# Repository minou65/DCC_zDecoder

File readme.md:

# DCC zDecoder

- [DCC zDecoder](#dcc-zdecoder)
	- [Beschreibung](#beschreibung)
	- [Platinen](#platinen)
	- [Librarys](#librarys)
	- [Pin mapping](#pin-mapping)
	- [Betriebsarten](#betriebsarten)
		- [in Vorbereitung](#in-vorbereitung)
	- [Schema](#schema)
	- [Materialliste](#materialliste)
	- [Anschlüsse](#anschlüsse)
	- [Inbetriebnahme](#inbetriebnahme)
	- [Web UI](#web-ui)
		- [Overview](#overview)
		- [Groups](#groups)
		- [Config](#config)
	- [WiFi](#wifi)
		- [Default Password](#default-password)
		- [Default IP address](#default-ip-address)
		- [OTA](#ota)
		- [Configuration options](#configuration-options)
		- [Blinking codes](#blinking-codes)
	- [Firmware](#firmware)
	- [Reset](#reset)

## Beschreibung
Das ist ein NRMA DCC dekoder basirend auf einem ESP32 NodeMCU. 
- Er kann bis zu 16 Ausgänge ansteuern. 
- Stellt eine Wifi AP zur verfügung oder kann in Wifi Netz integriert werden
- Wird via Web UI konfiguriert
- Kann via DCC oder Web UI gesteuert werden

Der Decoder kann an einer Spannung von 8 - 28V DC oder 18 - 36V AC betrieben werden. Pro Ausgang 
kann eine Last von 500mA geschaltet werden. Ist J1 auf der Stellung 5V, darf der gesamt Strom 1A
nicht übersteigen.

[Top of document](#dcc-zdecoder)

## Platinen
Unbestückte Platinen sind bei mir erhältlich für CHF 5.00 / Stück plus Porto. Bestückte Platinen CHF 30.00 plus Porto
[Top of document](#dcc-zdecoder)

## Librarys
Die folgenden Bibliotheken werden verwendet und müssen installiert werden
- [NMRA DCC](https://github.com/mrrwa/NmraDcc)
- [IotWebConf (3.2.3)](https://github.com/minou65/IotWebConf)
- [IotWebRoot](https://github.com/minou65/IotWebRoot)

[Top of document](#dcc-zdecoder)

## Pin mapping
In der Header datei [pinmapping.h](src/pinmapping.h) können die Pins für die 16 Ausgänge an die eigenen Bedürfnisse angepasst werden.

```cpp
static uint8_t ChannelToGPIOMapping[16] = {
	GPIO_NUM_23, // O11
	GPIO_NUM_22, // O12
	GPIO_NUM_21, // O13
	GPIO_NUM_19, // O14
	GPIO_NUM_18, // O15
	GPIO_NUM_17, // O16
	GPIO_NUM_16, // O17
	GPIO_NUM_4,  // O18

	GPIO_NUM_33, // O21
	GPIO_NUM_32, // O22
	GPIO_NUM_25, // O23
	GPIO_NUM_26, // O24
	GPIO_NUM_27, // O25
	GPIO_NUM_14, // O26
	GPIO_NUM_12, // O27
	GPIO_NUM_13  // O28

};
```
[Top of document](#dcc-zdecoder)

## Betriebsarten

Der zDecoder untersützt folgende Betriebsarten
- [Watchdog](doc/watchdog.md#watchdog-1)
- [einfacher Ausgang](doc/blinkers.md#einfacher-ausgang)
- [Blinker](doc/blinkers.md#blinker)
- [Wechselblinker](doc/blinkers.md#wechselblinker)
- [Fernseher](doc/blinkers.md#fernseher)
- [Schweisslicht](doc/blinkers.md#schweissen)
- [Feuer](doc/blinkers.md#feuer)
- [Blitzlicht](doc/blinkers.md#blitzlicht)
- [Lauflicht 1](doc/blinkers.md#lauflicht-1)
- [Lauflicht 2](doc/blinkers.md#lauflicht-2)
- [Lauflicht 3](doc/blinkers.md#lauflicht-3)
- [Lauflicht 4](doc/blinkers.md#lauflicht-4)
- [Hausbeleuchtung](doc/blinkers.md#hausbeleuchtung)
- [Neonlampen](doc/blinkers.md#neon-lampe)
- [Natriumlampen](doc/blinkers.md#natrium-lampe)
- [Entkuppler](doc/coils.md#entkuppler)
- [Weiche](doc/coils.md#weiche)
- [Servo](doc/servo.md#servo-1)

[Top of document](#dcc-zdecoder)

### in Vorbereitung
- SBB Hauptsignal 2 flammig
- SBB Hauptsignal 3 flammig
- SBB Hauptsignal 4 flammig
- SBB Hauptsignal 5 flammig
- SBB Zwergsignal
- Strassensignal

[Top of document](#dcc-zdecoder)

## Schema

## Materialliste

[Partliste](sch/partlist.txt)

[Top of document](#dcc-zdecoder)

## Anschlüsse

| Klemmenblock | Beschreibung |
| --- | --- |
| X1 - X2 | + Anschluss für Verbraucher 5/12-28VDc, je nach position von J1 |
| X3 - X4 | - Anschluss für Verbraucher |
| X5 | DCC signal |
| X6 | Anschluss versorgungspannung für Decoder und Verbraucher. 12 - 28VDC/AC |
| X7 - X12 | Anschluss für Servos |

[Top of document](#dcc-zdecoder)

## Inbetriebnahme

Nachdem alles zusammengebaut ist und alle Lötstellen sorgfältig überprüft wurden, kann das Program auf den ESP aufgespielt werden.
Lauflicht 2

[Top of document](#dcc-zdecoder)

## Web UI

Mittels des Web User interfaces kann der zDecoder einfach konfiguriert und bedient werden

### Overview

auf dieser Seite sind alle wichtigen Informationn zu zDecoder ersichtlich

[Top of document](#dcc-zdecoder)

### Groups

auf dieser Seite können die Gruppen ein und ausgescahltet werden. Wird über DCC geschaltet, ist auf dieser Seite auch der jeweilige Status ersichtlich. Rot ist ausgeschaltet, grün ist eingeschaltet

[Top of document](#dcc-zdecoder)

### Config

auf dieser Seite können die Gruppen erstellt und konfiguriert werden. Die Bedeutung und Verwendung der Parameter ist beim jeweiligen Objekt unter [Betriebsarten](#betriebsarten) beschrieben.

[Top of document](#dcc-zdecoder)

## WiFi

### Default Password

Wenn nicht mit einem AP verbunden, ist das Standardpasswort 123456789

[Top of document](#dcc-zdecoder)

### Default IP address

Wenn nicht mit einem AP verbunden, ist die IP Adresse 192.168.4.1

[Top of document](#dcc-zdecoder)

### OTA 
OTA ist aktiviert und kann verwenbdet werden. Damit ist es möglich, die Software des zDecoders zu updaten ohne unter die Anlage krichen zu müssen. Die IP Adresse ist entweder die Default IP address oder die vom AP zugewissene. Port ist Standart

[Top of document](#dcc-zdecoder)

### Configuration options
Nach dem ersten Start müssen einige Werte eingerichtet werden.

| Parameter | Beschreibung |
|---|---|
| Thing name | Name des Decoders. Es sollten keine Sonderzeichen und <br> Umlaute verwendet werden. Punkte und Leerzeichen sollten <br> ebenfalls nicht verwendet werden.
| AP password | Dieses Passwort wird verwendet, wenn Sie später auf <br> das Gerät zugreifen möchten. Sie müssen ein Passwort <br> mit mindestens 8, höchstens 32 Zeichen verwenden. <br> Es steht Ihnen frei, beliebige Zeichen zu verwenden, <br> Es sollte ein Passwort mit mindestens 12 Zeichen Länge gewählt werden. |
| WiFi SSID | Name des WLan mit welchem das thing verwendet werden soll. |
| WiFi password | Das Passwort zum Netzwerk, mit welchem das Thing verbunden werden soll. |

[Top of document](#dcc-zdecoder)

### Blinking codes

In der nachfolgenden Tabelle fasst die verschiedenen Blinkcodes zusammen

| Code | Bedeutung |
|---|---|
| rasches blinken | meisten ein, unterbrochen durch kurze aus perioden. <br> Eigener AP ist aktiviert und sie können mit <br> dem Smartphone oder einem Computer eine<br> Verbindung zum Thing herstellen. |
| wechsel blinken | Das Thing versucht mit einem AP zu verbinden |
| langsames blinken | meistens aus mit kurzem blinken <br> Das Thing ist online und mit dem WLan verbunden |

[Top of document](#dcc-zdecoder)

## Firmware
Hier kann, eine entsprechende Datei vorausgesetzt, die Firmware des decoders aktualisiert werden

## Reset
Wurde das Passwort vergessen oder funktioniert der Decoder nicht mehr kann durch schliessen des Jumpers Reset während dem booten, der Decoder auf die Werkseinstellungen zurückgesetzt werden.

[Top of document](#dcc-zdecoder)

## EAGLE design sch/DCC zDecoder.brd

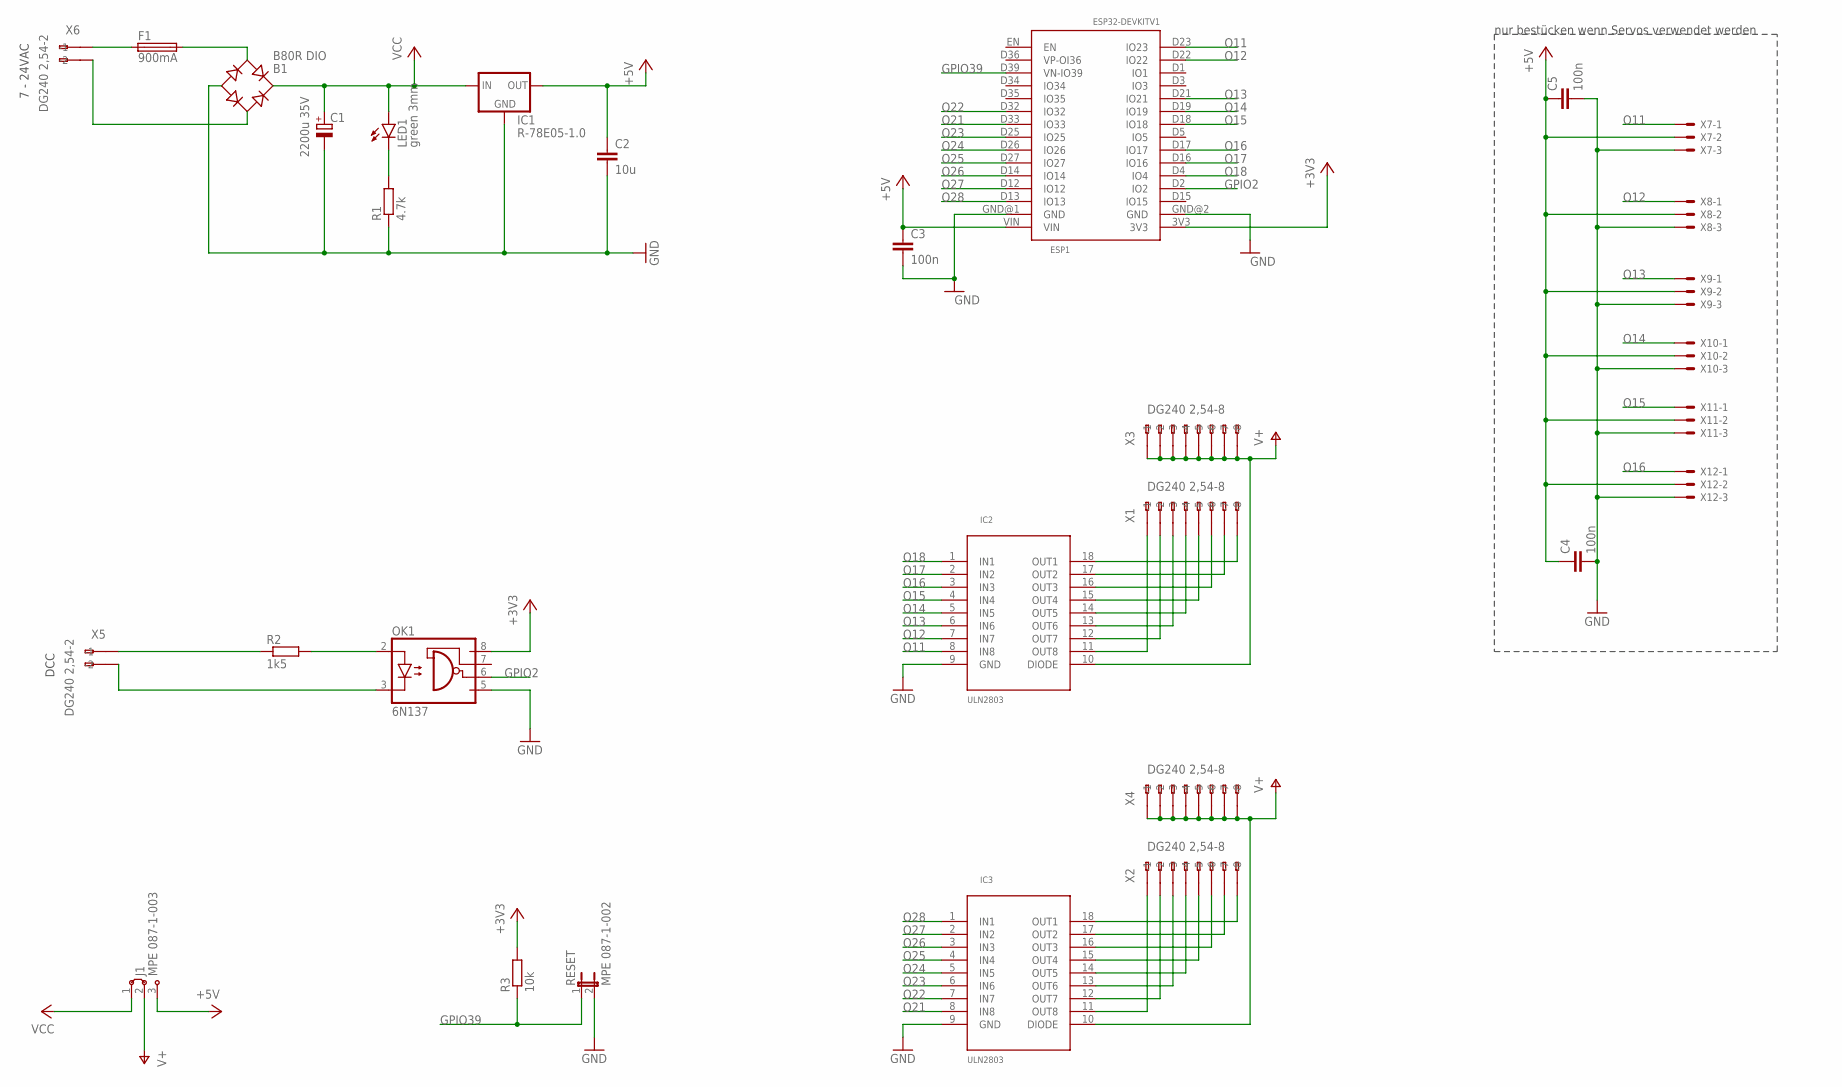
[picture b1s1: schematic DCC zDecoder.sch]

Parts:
B1: B80R DIO; RB1A
C1: 2200u 35V; E5-8,5
C2: 10u; C050-024X044
C3, C4, C5: 100n; C050-024X044
ESP1: ESP32DEVKITV1; ESP32-DEVKITV1
F1: 900mA; TE5
IC1: R-78E05-1.0; R-78E-XX1.0
IC2, IC3: ULN2803; DIL18
J1: MPE 087-1-003; 04C
LED1: green 3mm; LED3MM
OK1: 6N137; DIL08
R1: 4.7k; 0207/10
R2: 1k5; 0207/10
R3: 10k; 0207/10
RESET: MPE 087-1-002; JP1
X1, X2, X3, X4: DG240 2,54-8; 233-508
X5, X6: DG240 2,54-2; 233-202
X7, X8, X9, X10, X11, X12: PSS 254/3G; 22-23-2031

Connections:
+3V3: ESP1.3V3, OK1.8 (VCC), R3.2
+5V: C2.1, C3.1, C4.1, C5.1, ESP1.VIN, IC1.OUT, J1.3, X7.2, X8.2, X9.2, X10.2, X11.2, X12.2
GND: B1.-, C1.-, C2.2, C3.2, C4.2, C5.2, ESP1.GND@1 (GND), ESP1.GND@2 (GND), IC1.GND, IC2.9 (GND), IC3.9 (GND), OK1.5 (GND), R1.1, RESET.2, X7.3, X8.3, X9.3, X10.3, X11.3, X12.3
GPIO2: ESP1.D2 (IO2), OK1.6 (VO)
GPIO39: ESP1.D39 (VN-IO39), R3.1, RESET.1
unnamed: IC2.11 (OUT8), X1.A1 (-1)
unnamed: IC2.12 (OUT7), X1.A2 (-2)
unnamed: LED1.K (C), R1.2
unnamed: IC2.13 (OUT6), X1.A3 (-3)
unnamed: B1.AC1, F1.2
unnamed: B1.AC2, X6.A2 (-2)
unnamed: IC2.14 (OUT5), X1.A4 (-4)
unnamed: IC2.15 (OUT4), X1.A5 (-5)
unnamed: R2.1, X5.A1 (-1)
unnamed: OK1.2 (A), R2.2
unnamed: OK1.3 (C), X5.A2 (-2)
unnamed: IC2.16 (OUT3), X1.A6 (-6)
unnamed: IC2.17 (OUT2), X1.A7 (-7)
unnamed: IC2.18 (OUT1), X1.A8 (-8)
unnamed: F1.1, X6.A1 (-1)
unnamed: IC3.18 (OUT1), X2.A8 (-8)
unnamed: IC3.17 (OUT2), X2.A7 (-7)
unnamed: IC3.16 (OUT3), X2.A6 (-6)
unnamed: IC3.15 (OUT4), X2.A5 (-5)
unnamed: IC3.14 (OUT5), X2.A4 (-4)
unnamed: IC3.13 (OUT6), X2.A3 (-3)
unnamed: IC3.12 (OUT7), X2.A2 (-2)
unnamed: IC3.11 (OUT8), X2.A1 (-1)
O11: ESP1.D23 (IO23), IC2.8 (IN8), X7.1
O12: ESP1.D22 (IO22), IC2.7 (IN7), X8.1
O13: ESP1.D21 (IO21), IC2.6 (IN6), X9.1
O14: ESP1.D19 (IO19), IC2.5 (IN5), X10.1
O15: ESP1.D18 (IO18), IC2.4 (IN4), X11.1
O16: ESP1.D17 (IO17), IC2.3 (IN3), X12.1
O17: ESP1.D16 (IO16), IC2.2 (IN2)
O18: ESP1.D4 (IO4), IC2.1 (IN1)
O21: ESP1.D33 (IO33), IC3.8 (IN8)
O22: ESP1.D32 (IO32), IC3.7 (IN7)
O23: ESP1.D25 (IO25), IC3.6 (IN6)
O24: ESP1.D26 (IO26), IC3.5 (IN5)
O25: ESP1.D27 (IO27), IC3.4 (IN4)
O26: ESP1.D14 (IO14), IC3.3 (IN3)
O27: ESP1.D12 (IO12), IC3.2 (IN2)
O28: ESP1.D13 (IO13), IC3.1 (IN1)
V+: IC2.10 (DIODE), IC3.10 (DIODE), J1.2, X3.A1 (-1), X3.A2 (-2), X3.A3 (-3), X3.A4 (-4), X3.A5 (-5), X3.A6 (-6), X3.A7 (-7), X3.A8 (-8), X4.A1 (-1), X4.A2 (-2), X4.A3 (-3), X4.A4 (-4), X4.A5 (-5), X4.A6 (-6), X4.A7 (-7), X4.A8 (-8)
VCC: B1.+, C1.+, IC1.IN, J1.1, LED1.A

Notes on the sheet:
7 - 24VAC
DCC
nur bestücken wenn Servos verwendet werden

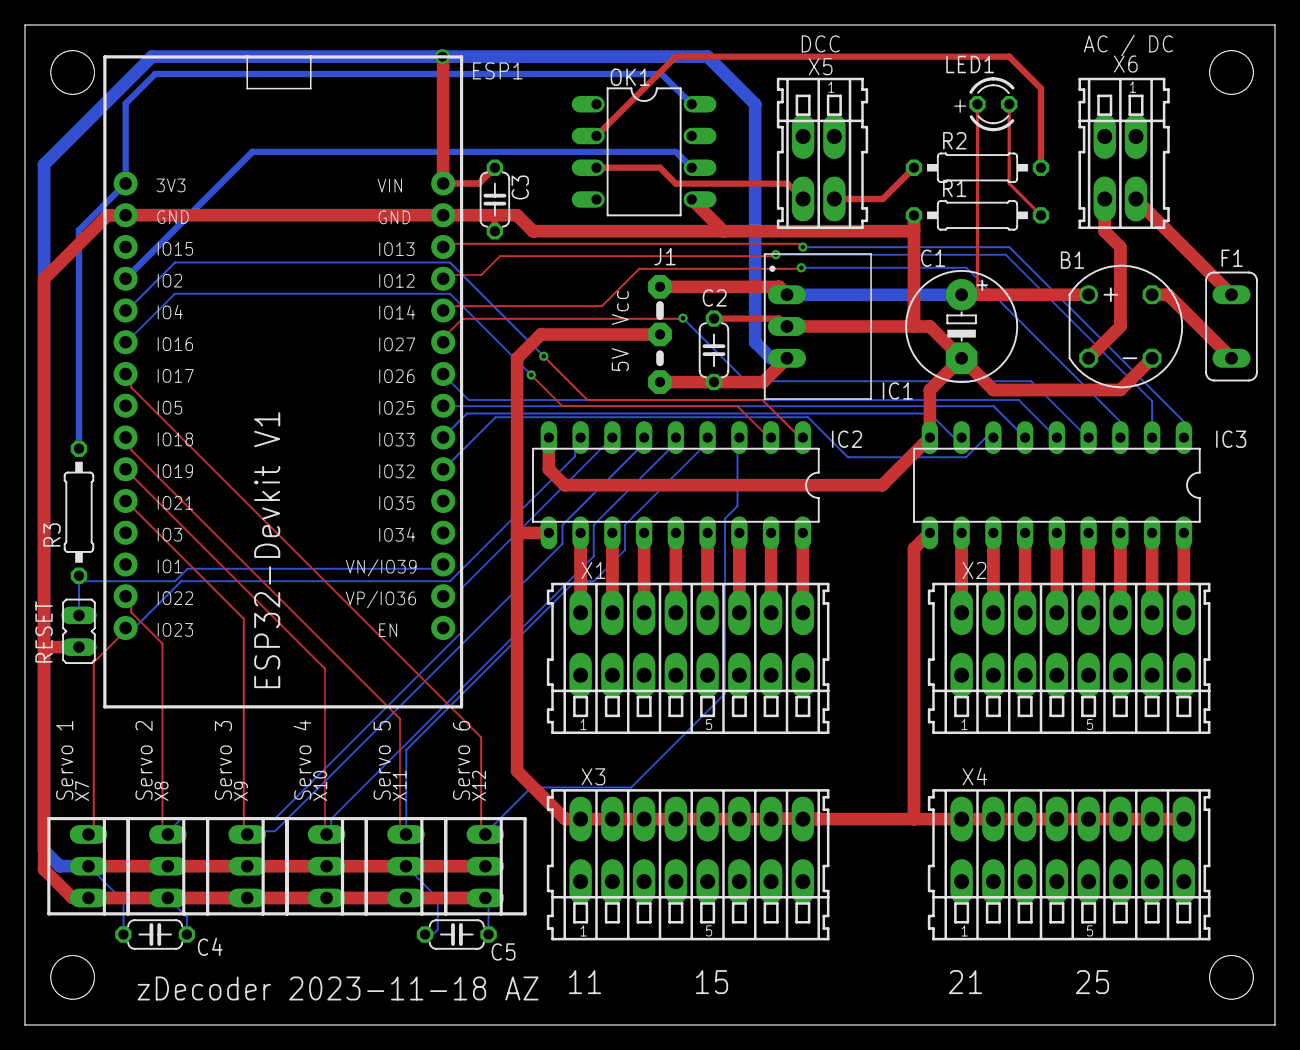
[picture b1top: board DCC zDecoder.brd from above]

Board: 2 copper layers, 100.0 x 80.0 mm, 30 parts (0 on the bottom side), 46 nets.

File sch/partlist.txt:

Partlist

Exported from DCC zDecoder.sch at 18.11.2023 09:42

EAGLE Version 9.6.2 Copyright (c) 1988-2020 Autodesk, Inc.

Assembly variant: 

Part     Value          Device        Package        Library     Sheet

B1       B80R DIO       RB1A          RB1A           rectifier   1
C1       2200u 35V      CPOL-EUE5-8.5 E5-8,5         rcl         1
F1       900mA          TE5           TE5            fuse        1
IC1      TSR 1-2450     78XXS         78XXS          v-reg       1
IC2      ULN2803        ULN2803DIL18  DIL18          _eigene     1
IC3      ULN2803        ULN2803DIL18  DIL18          _eigene     1
J1       MPE 087-1-003  J2X2MM        04C            jumper      1
LED1     green 3mm      TLLG4400      LED3MM         led         1
OK1      6N137          6N137         DIL08          optocoupler 1
R1       4.7k           R-EU_0207/10  0207/10        rcl         1
R2       1k5            R-EU_0207/10  0207/10        rcl         1
R3       10k            R-EU_0207/10  0207/10        rcl         1
RESET    MPE 087-1-002  JP1E          JP1            jumper      1
U$1      ESP32DEVKITV1  ESP32DEVKITV1 ESP32-DEVKITV1 _esp32      1
X1       DG240 2,54-8   233-508       233-508        con-wago255 1
X2       DG240 2,54-8   233-508       233-508        con-wago255 1
X3       DG240 2,54-8   233-508       233-508        con-wago255 1
X4       DG240 2,54-8   233-508       233-508        con-wago255 1
X5       DG240 2,54-2   233-202       233-202        con-wago255 1
X6       DG240 2,54-2   233-202       233-202        con-wago255 1
X7       PSS 254/3G     22-23-2031    22-23-2031     con-molex   1
X8       PSS 254/3G     22-23-2031    22-23-2031     con-molex   1
X9       PSS 254/3G     22-23-2031    22-23-2031     con-molex   1
X10      PSS 254/3G     22-23-2031    22-23-2031     con-molex   1
X11      PSS 254/3G     22-23-2031    22-23-2031     con-molex   1
X12      PSS 254/3G     22-23-2031    22-23-2031     con-molex   1

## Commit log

2023-10-27 initial version
2023-10-27 inital version
2023-10-27 led2 and led3 should be on
2023-10-27 added new file
2023-10-27 added values
2023-10-27 added file
2023-10-28 reneamed some variables
2023-10-28 updated list
2023-10-29 addes support for servo
2023-10-29 updated websites
2023-10-29 added dual core support
2023-10-29 PWMFrequency changed
2023-10-29 start blinker without delay
2023-10-29 added class CustomHtmlFormatProvider
2023-10-30 new file
2023-10-30 added support for hiding elements
2023-10-30 fixed problem where onload is not working
2023-10-31 Mode 0 for not anymore used channels added
2023-10-31 added Watchdog
2023-10-31 support watchdog added
2023-11-01 GPIO assigment changed
2023-11-01 parent class changed
2023-11-01 reset pin changed
2023-11-02 destructors added
2023-11-02 config pin added
2023-11-04 reset pin added and pin mapping changed
2023-11-04 dctor changed
2023-11-04 config pin config mouved to common.h
2023-11-04 added definition for config_pin
2023-11-05 Decoder reset added
2023-11-05 file removed
2023-11-05 support for servos added
2023-11-06 included servo lib as ESPServo in project
2023-11-06 added some infos
2023-11-06 changed class and include to new lib
2023-11-09 added servogroup reset and set group inactive
2023-11-09 variable renamed
2023-11-10 Lauflicht 4 added
2023-11-10 infos added
2023-11-10 fixed nullptr exception
2023-11-10 Blitzlicht added
2023-11-10 set all ports to output an disable them
2023-11-10 status changed
2023-11-11 updated Lauflicht 4
2023-11-11 added Blitzlicht
2023-11-11 help updated
2023-11-11 javascript simplified
2023-11-11 partlist updated
2023-11-12 files moved to doc folder
2023-11-13 links updated
2023-11-17 config version incresed
2023-11-17 nulpointer error fixed
2023-11-17 pins changed
2023-11-17 groups page changed
2023-11-17 number of outputs changed
2023-11-18 backup
2023-11-18 fixed bug in Lauflicht4
2023-11-18 routing changed and fuse added
2023-11-18 list updated
2023-11-19 Version 1.0
2023-11-19 new file added
2023-12-10 IC Sockel geändert
2023-12-10 Materialliste hinzugrfügt
2023-12-10 Outputs an PCB angepasst
2023-12-16 pin mapping
2023-12-17 modifiyed notifyTurnoutAddress for correct DCC handling
2023-12-17 modifyed notifyAddress for correct DCC handling
2023-12-17 corrected some typos
2023-12-17 notify functions as virtual
2023-12-17 notifiy functions as extern declared
2023-12-17 removed notifyDccMsg and some typos fixed
2023-12-17 readme extended
2024-03-24 update firmware added to config page
2024-03-24 Dependency on server.h removed
2024-03-24 thing name changed
2024-03-24 Version 1.0.0.2
2024-03-24 firmware updated added
2024-03-29 license added
2024-06-23 added new version handling
2024-06-26 removed defines for html code
2024-06-26 moved to espasyncserver
2024-06-26 reformated Javascript function hideclass
2024-06-26 removed typo
2024-06-27 html code moved to html.c
2024-06-27 fixed some typos
2024-06-27 enable / disable all added
2024-09-29 Revert "license added"
    This reverts commit 608e883abfa1eb2cf6ff0a47de84883c0d001d60.
2024-09-29 file added to gitignore
2024-09-29 moved some strings to html.h
2024-10-01 migratet to new version ESPAsyncWebServer. Added some error handling for more stability
2024-10-02 handlers for data and post added
2024-10-04 reverted to af8624b
2024-10-04 reverted to 39b983b
2024-10-04 auto version handling added
2024-10-04 moved IOTWEBCONF_HTML_FORM_InputElements_JAVASCRIPT to html.c
2024-10-04 form validator removed
2024-10-04 new root page
2024-10-05 page settings added
2024-10-05 handleData added
2024-10-05 cleanup
2024-10-05 handlePost added
2024-10-05 test if channel is valid or not
2024-10-05 all on/off added to main page
2024-10-05 Linke to home page added
2024-10-05 enable / disable all channels
2024-10-05 on config page link to home page added
2024-10-05 favicon added
2024-10-05 version 1.1.0
2024-11-09 Add brightness parameter to web handling configuration
2024-11-09 Add brightness control to LED class
2024-11-09 Refactor LED class member variables for clarity and consistency
2024-11-09 Refactor LEDFader and Neon classes for improved variable naming consistency
2024-11-09 Renamed some vatiables for better reading
2024-11-10 Add AccessoryType enum and implement getType method in accessories and Signal classes
2024-11-10 Implement Coil class as an accessory and add getType method
2024-11-10 Refactor LED class to inherit from accessories and implement getType method
2024-11-10 Refactor ServoControl class to inherit from accessories and implement getType method
2024-11-10 Implement getType method in Watchdog class to return AccessoryType
2024-11-10 Add brightness visibility logic based on selectedValue in hideClass function
2024-11-10 Add brightness handling for LED accessories in zDecoderInit function
2024-11-10 Add brightness parameter to blinker documentation
2024-11-10 Refactor status indicator pin definitions for clarity and consistency
2024-11-10 Add debug print statement to getType method in Accessory class
2024-11-10 Refactor accessory classes to inherit from LEDaccessories and add SetMaxBrightness method
2024-11-10 Add LEDaccessories class with SetMaxBrightness method and refactor LED class
2024-11-10 Fix LED accessory type check and update brightness setting logic
2024-11-10 ajax handling improved
2024-11-10 fixed form id and button id to be unique
2024-11-10 fixed bug where button assigment to decodergroups was not correct
2024-11-10 removed some debug messages
2024-11-11 Refactor status pin handling and update ON_LEVEL definition
2024-11-11 Improve form submission feedback and calling requestData
2024-11-11 format RSSI data as a string in JSON response
2024-11-11 Add SetMaxBrightness method to Feuer and Blitzlicht classes
2024-11-13 Add handleConfigSavedPage function to redirect after saving configuration
2024-11-13 Add handleConfigSavedPage function to handle redirection after configuration save
2024-11-15 Add handling for missing AP password and unconfigured SSID pages
2024-11-15 Add reset functionality to web handling with AJAX support
2024-11-15 Update README.md to include library links and versions
2024-11-15 Refactor LED accessory handling in zDecoderInit to remove redundant type check
2024-11-16 Add Content-Length header and refactor response handling in web functions
2024-11-16 move html code to html.h
2024-11-17 Add response messages for SSID not configured and config saved pages
2024-11-17 Fix string concatenation in updateData function for consistent formatting
2024-11-17 Add getType method to UnCoupler and Turnout classes for accessory type retrieval
2024-11-17 Refactor UnCoupler class to use consistent parameter naming and add direction management
2024-11-18 Refactor Turnout class to improve parameter naming and enhance direction management
2024-12-18 Refactor ESPServo class to update LEDC channel attachment methods
2024-12-18 Refactor LED class to update LEDC channel attachment methods
2024-12-18 Refactor Turnout and TurnoutServo classes to use F() macro for string literals in Serial prints
2024-12-18 Refactor pinmapping.h to store ChannelToGPIOMapping in PROGMEM for improved memory efficiency
2024-12-18 Refactor webhandling to remove ESP8266 support and update Multiplier parameter range
2024-12-18 Update version to 1.2.10.737 with new build date and time
2025-05-30 Add convertSettings function to configure ArduinoOTA hostname
2025-05-30 Update version to 1.2.11.740 with new build time
2025-07-31 Refactor: moved to ESP32-DecoderCore
2025-07-31 Refactor: rename ChannelToGPIOMapping to OutputIndexToPin for clarity
2025-08-07 Add DecoderCoreConfig.h for configuration settings
2025-08-07 Refactor: update OutputModeValues and OutputModeNames for clarity and consistency
2025-08-07 Refactor: update HTML button elements for consistency and improved styling
2025-08-07 Add PinGroup enum and getPinFromIndex function for pin retrieval
2025-08-07 Refactor: removed ServoGroup tand update parameter handling
2025-08-07 Refactor: update webhandling.cpp for improved structure and consistency
2025-08-07 Refactor: streamline zDecoder.ino by removing unused code switching to ESP32_DecoderCore lib
2025-08-10 Refactor: use ESPAsyncWebServer
2025-08-10 Update version.h for version 1.4.0.873 release
2025-08-25 Refactor: remove unused output mode "70" and reorder output mode entries in common.h
2025-08-25 Refactor: remove unused values from show arrays in hideClass function
2025-08-25 Refactor: add ShouldReboot flag and update websetup to use AsyncWebRequestWrapper
2025-08-25 Refactor: remove LittleFS initialization and file deletion logic from websetup function
2025-08-25 Refactor: enhance accessory creation logic to support servo modes
2025-08-25 Refactor: add Thing name display to root and settings pages
2025-11-03 feat: add inputhandling
2025-11-03 fix: update AsyncWebRequestWrapper initialization to include buffer size parameter
2025-11-08 Refactor: correct comments and adjust input pin values in common.h
2025-11-08 Refactor: uncomment Input Pin and Edge Type parameters in OutputGroup
2025-11-08 Refactor: comment out OutputGroup10 linkage and simplify AsyncWebRequestWrapper creation
2025-11-09 feat: add logging for input accessory creation in zDecoderInit
2025-11-09 feat: enable IotWebConfAsync debugging and remove cleanup wrappers from web loop
2026-01-09 Refactor: migrate to AsyncIotWebConf library
2026-01-11 feat: update IotWebConf to AsyncIotWebConf and enable additional OutputGroups
2026-01-23 feat: update version to 1.5.1 with new build details
2026-01-24 feat: enhance OutputGroup constructor to include labels for better clarity
2026-01-24 fix: refactor handlePost to iterate through all OutputGroups for on/off commands
